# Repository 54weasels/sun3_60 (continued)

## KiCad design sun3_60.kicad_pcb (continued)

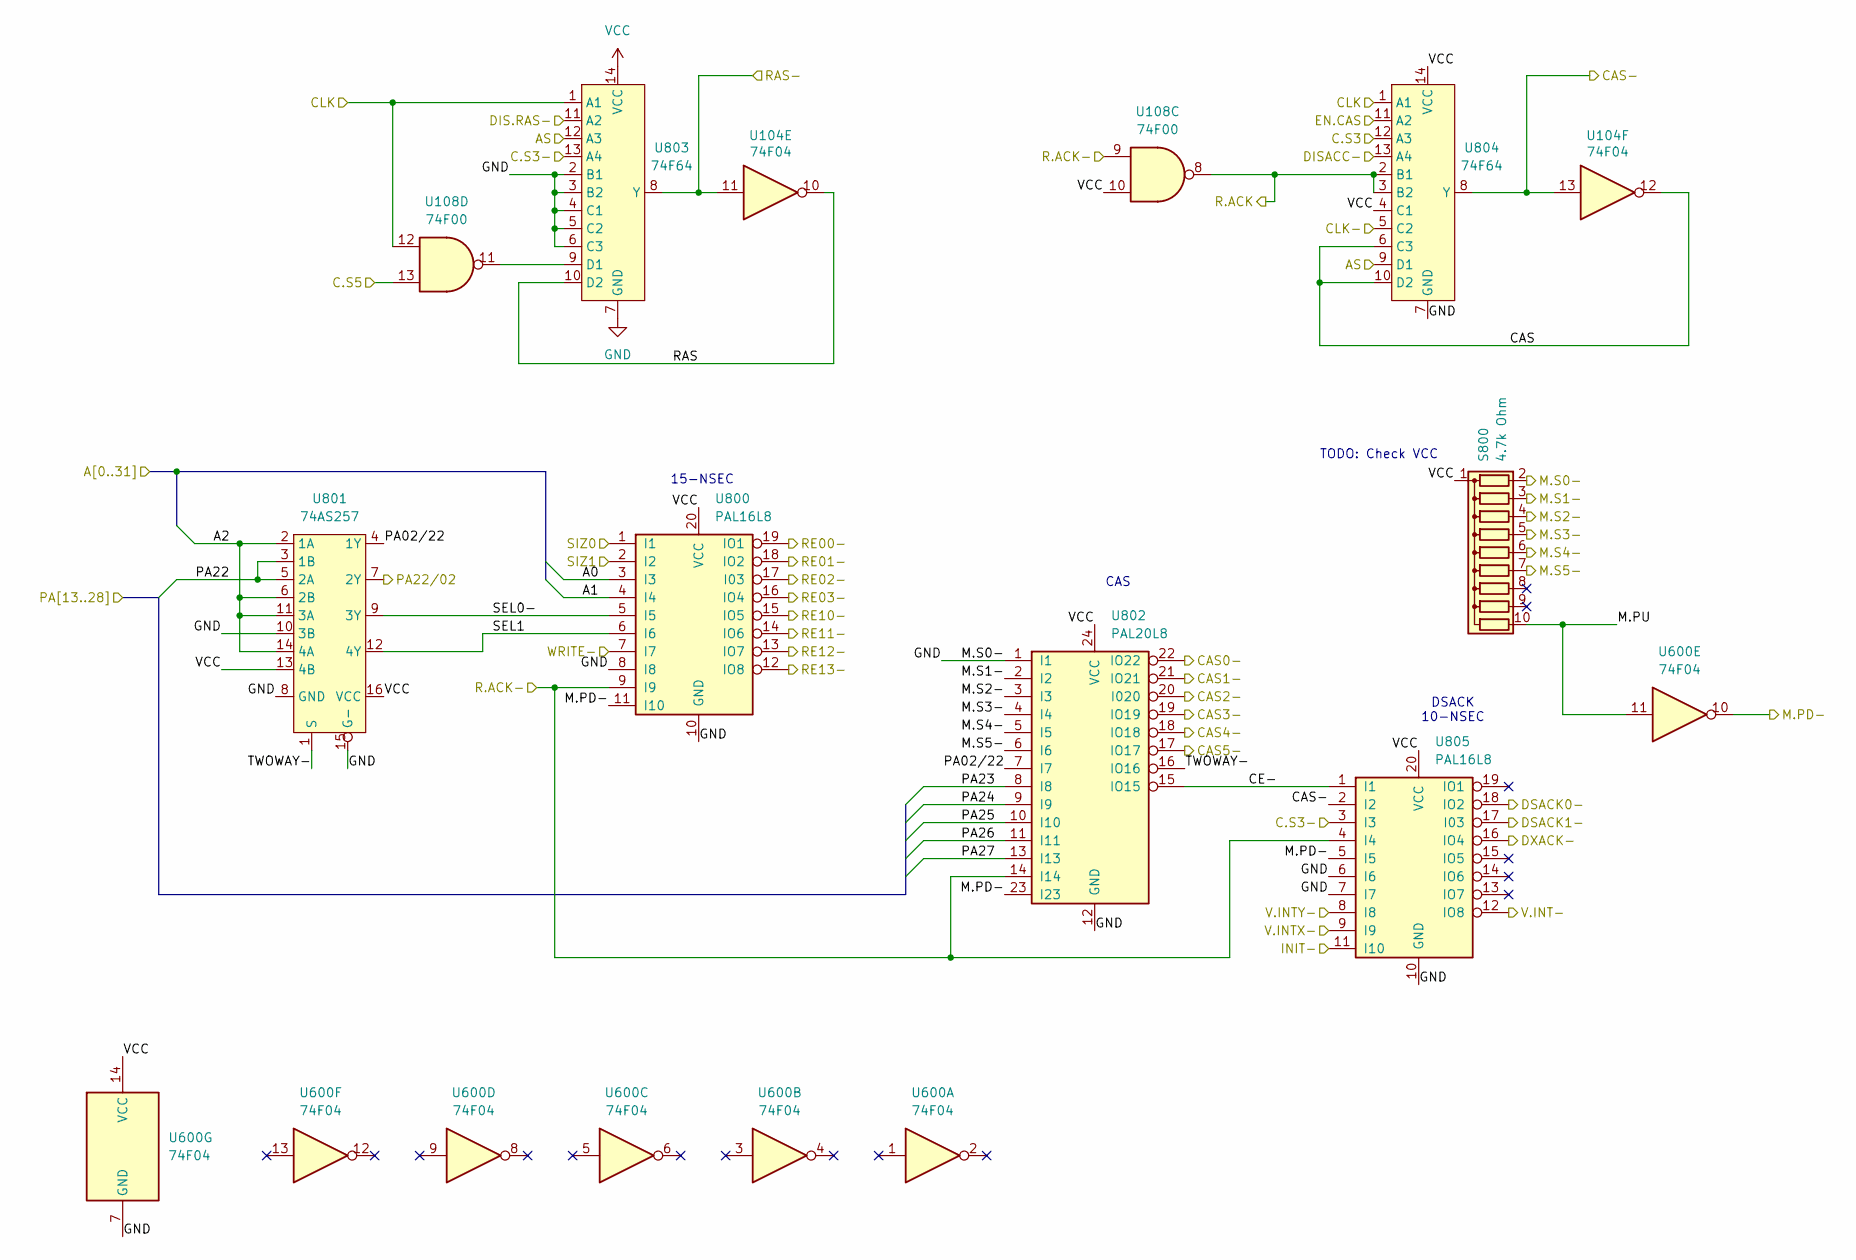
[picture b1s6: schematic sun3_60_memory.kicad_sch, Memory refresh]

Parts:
S800: 4.7k Ohm; R_Array_SIP10
U104, U600: 74F04; DIP-14_W7.62mm
U108: 74F00; DIP-14_W7.62mm
U800, U805: PAL16L8; DIP-20_W7.62mm
U801: 74AS257; DIP-16_W7.62mm
U802: PAL20L8; DIP-24_W7.62mm
U803, U804: 74F64; DIP-14_W7.62mm

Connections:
/AS: U803.12 (A3), U804.9 (D1); also elsewhere on the board
/C.S3: U804.12 (A3); also elsewhere on the board
/C.S3-: U803.13 (A4), U805.3 (I3); also elsewhere on the board
/C.S5: U108.13; also elsewhere on the board
/CAS-: U104.13, U804.8 (Y), U805.2 (I2); also elsewhere on the board
/CLK: U108.12, U803.1 (A1), U804.1 (A1); also elsewhere on the board
/CLK-: U804.5 (C2); also elsewhere on the board
/DIS.RAS-: U803.11 (A2); also elsewhere on the board
/DISACC-: U804.13 (A4); also elsewhere on the board
/DSACK0-: U805.18 (IO2); also elsewhere on the board
/DSACK1-: U805.17 (I03); also elsewhere on the board
/DXACK-: U805.16 (IO4); also elsewhere on the board
/EN.CAS: U804.11 (A2); also elsewhere on the board
/Ethernet/A0: U800.3 (I3); also elsewhere on the board
/Ethernet/A1: U800.4 (I4); also elsewhere on the board
/Ethernet/A2: U801.2 (1A), U801.6 (2B), U801.11 (3A), U801.14 (4A); also elsewhere on the board
/INIT-: U805.11 (I10); also elsewhere on the board
/R.ACK-: U108.9, U800.9 (I9), U802.14 (I14), U805.4 (I4); also elsewhere on the board
/S8A Memory/CAS: U104.12, U804.6 (C3), U804.10 (D2)
/S8A Memory/CAS0-: U802.22 (IO22); also elsewhere on the board
/S8A Memory/CAS1-: U802.21 (IO21)
/S8A Memory/CAS2-: U802.20 (I020)
/S8A Memory/CAS3-: U802.19 (IO19)
/S8A Memory/CAS4-: U802.18 (IO18)
/S8A Memory/CAS5-: U802.17 (IO17)
/S8A Memory/CE-: U802.15 (IO15), U805.1 (I1)
/S8A Memory/M.PD-: U600.10, U800.11 (I10), U802.23 (I23), U805.5 (I5); also elsewhere on the board
/S8A Memory/M.PU: S800.10 (R9), U600.11
/S8A Memory/M.S1-: S800.3 (R2), U802.2 (I2)
/S8A Memory/M.S2-: S800.4 (R3), U802.3 (I3)
/S8A Memory/M.S3-: S800.5 (R4), U802.4 (I4)
/S8A Memory/M.S4-: S800.6 (R5), U802.5 (I5)
/S8A Memory/M.S5-: S800.7 (R6), U802.6 (I6)
/S8A Memory/PA02/22: U801.4 (1Y), U802.7 (I7)
/S8A Memory/PA22: U801.3 (1B), U801.5 (2A); also elsewhere on the board
/S8A Memory/PA22/02: U801.7 (2Y); also elsewhere on the board
/S8A Memory/PA23: U802.8 (I8); also elsewhere on the board
/S8A Memory/PA24: U802.9 (I9); also elsewhere on the board
/S8A Memory/PA25: U802.10 (I10); also elsewhere on the board
/S8A Memory/PA26: U802.11 (I11); also elsewhere on the board
/S8A Memory/PA27: U802.13 (I13); also elsewhere on the board
/S8A Memory/R.ACK: U108.8, U804.2 (B1), U804.3 (B2)
/S8A Memory/RAS: U104.10, U803.10 (D2)
/S8A Memory/RAS-: U104.11, U803.8 (Y); also elsewhere on the board
/S8A Memory/RE00-: U800.19 (IO1); also elsewhere on the board
/S8A Memory/RE01-: U800.18 (IO2); also elsewhere on the board
/S8A Memory/RE02-: U800.17 (I03); also elsewhere on the board
/S8A Memory/RE03-: U800.16 (IO4); also elsewhere on the board
/S8A Memory/RE10-: U800.15 (IO5)
/S8A Memory/RE11-: U800.14 (IO6)
/S8A Memory/RE12-: U800.13 (IO7)
/S8A Memory/RE13-: U800.12 (IO8)
/S8A Memory/SEL0-: U800.5 (I5), U801.9 (3Y)
/S8A Memory/SEL1: U800.6 (I6), U801.12 (4Y)
/S8A Memory/TWOWAY-: U801.1 (S), U802.16 (IO16)
/S8A Memory/V.INTX-: U805.9 (I9)
/S8A Memory/V.INTY-: U805.8 (I8)
/SIZ0: U800.1 (I1); also elsewhere on the board
/SIZ1: U800.2 (I2); also elsewhere on the board
/V.INT-: U805.12 (IO8); also elsewhere on the board
/WRITE-: U800.7 (I7); also elsewhere on the board
GND: S800.2 (R1), U600.7 (GND), U800.8 (I8), U800.10 (GND), U801.8 (GND), U801.10 (3B), U801.15 (G-), U802.1 (I1), U802.12 (GND), U803.2 (B1), U803.3 (B2), U803.4 (C1), U803.5 (C2), U803.6 (C3), U803.7 (GND), U804.7 (GND), U805.6 (I6), U805.7 (I7), U805.10 (GND); also elsewhere on the board
unnamed: U108.11, U803.9 (D1)
VCC: S800.1 (common), U108.10, U600.14 (VCC), U800.20 (VCC), U801.13 (4B), U801.16 (VCC), U802.24 (VCC), U803.14 (VCC), U804.4 (C1), U804.14 (VCC), U805.20 (VCC); also elsewhere on the board

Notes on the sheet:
DSACK 10-NSEC
TODO: Check VCC
CAS
15-NSEC

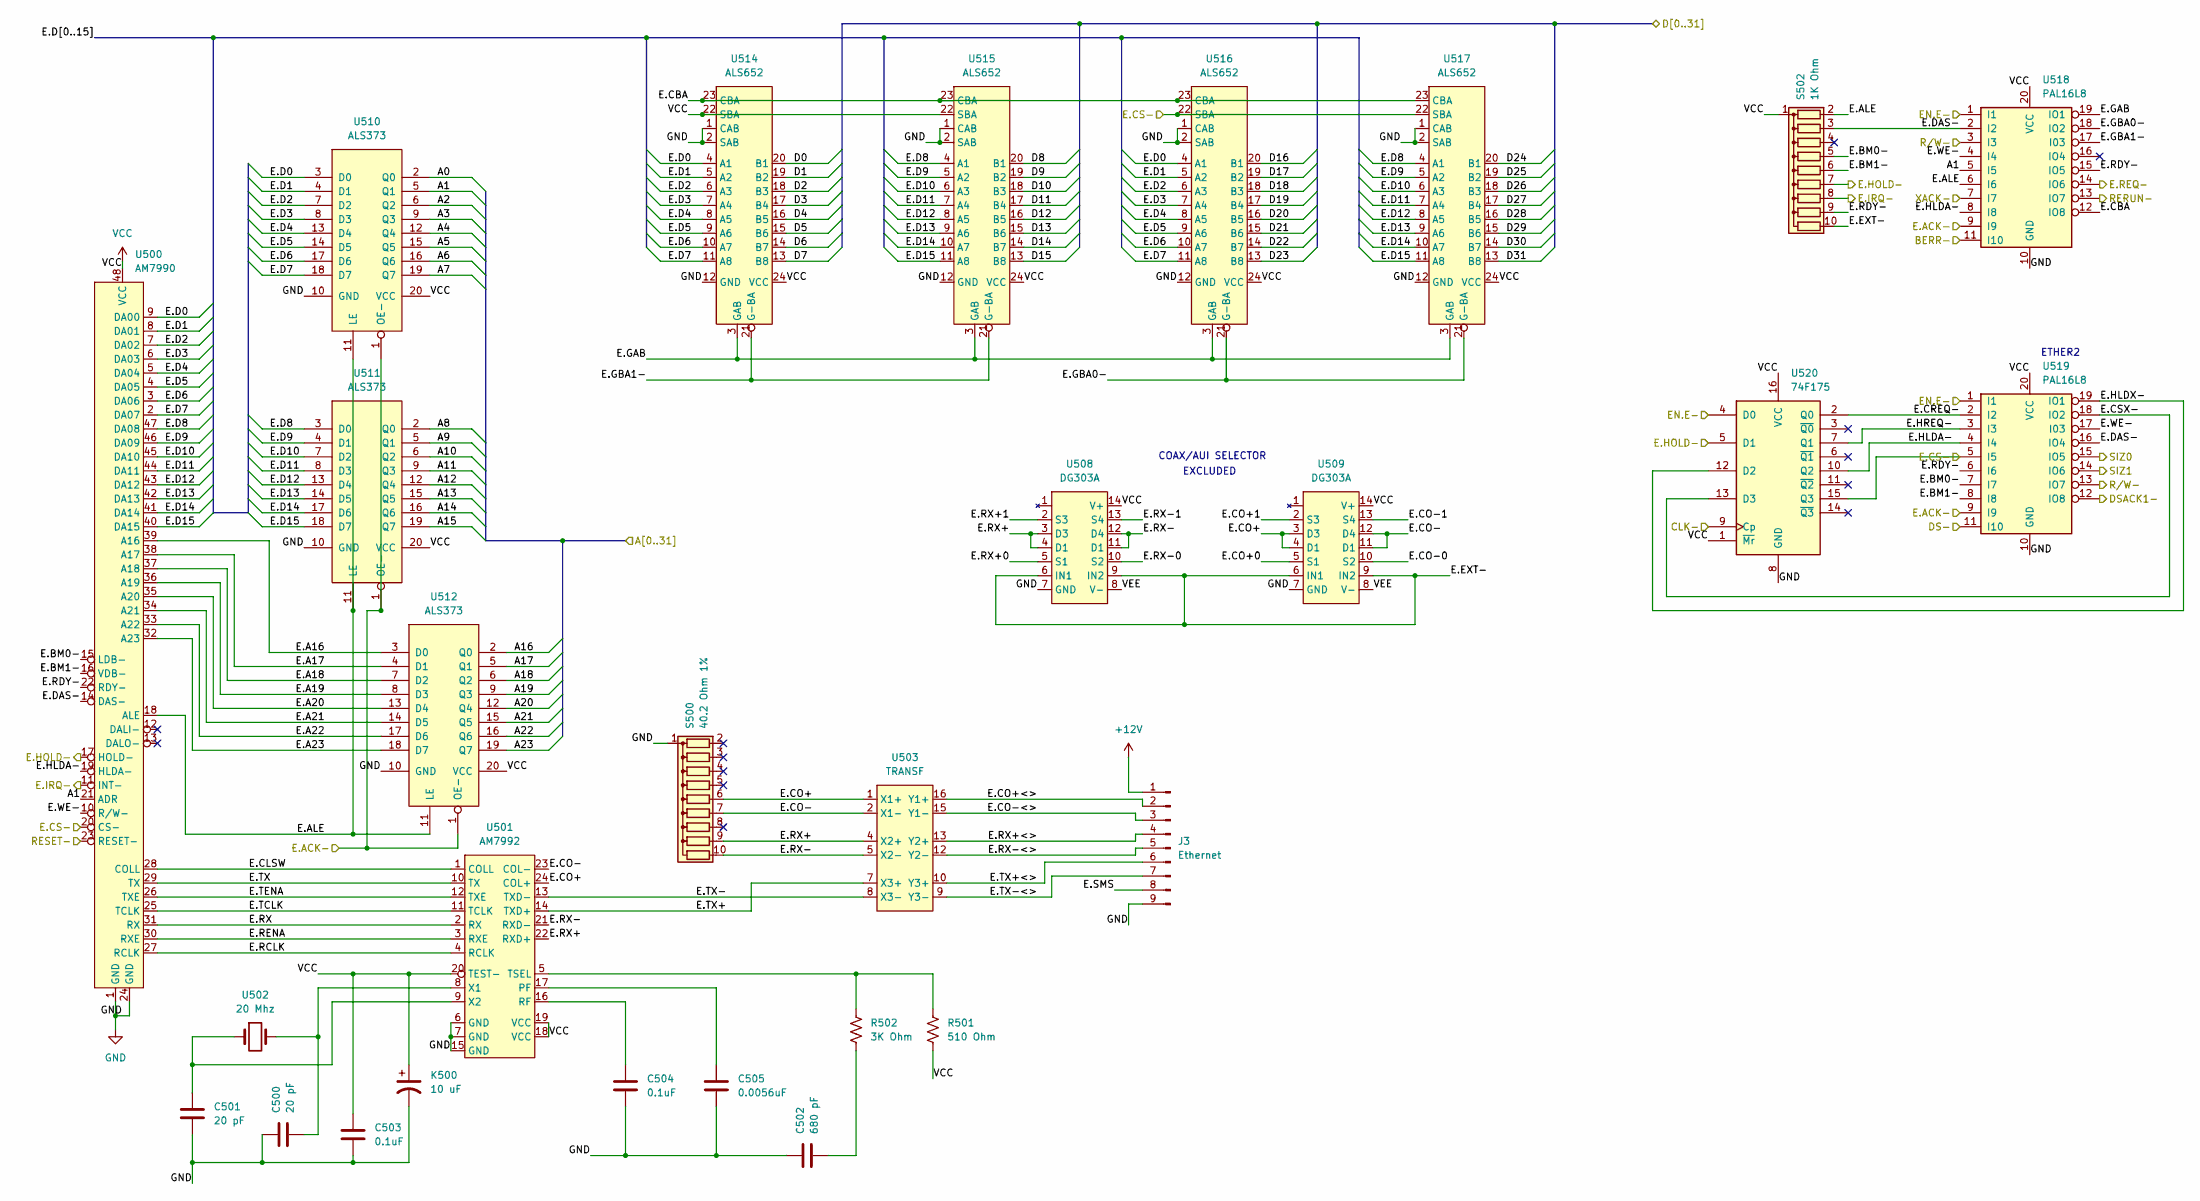
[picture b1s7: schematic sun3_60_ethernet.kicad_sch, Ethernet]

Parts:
C500, C501: 20 pF; C_Rect_L7.0mm_W2.0mm_P5.00mm
C502: 680 pF; C_Rect_L7.0mm_W2.0mm_P5.00mm
C503, C504: 0.1uF; C_Rect_L7.0mm_W2.0mm_P5.00mm
C505: 0.0056uF; C_Rect_L7.0mm_W2.0mm_P5.00mm
J3: Ethernet; PinHeader_1x09_P2.54mm_Vertical
K500: 10 uF; CP_Radial_D10.0mm_P5.00mm
R501: 510 Ohm; R_Axial_DIN0207_L6.3mm_D2.5mm_P7.62mm_Horizontal
R502: 3K Ohm; R_Axial_DIN0207_L6.3mm_D2.5mm_P7.62mm_Horizontal
S500: 40.2 Ohm 1%; R_Array_SIP10
S502: 1K Ohm; R_Array_SIP10
U500: AM7990; DIP-48_W15.24mm
U501: AM7992; DIP-24_W7.62mm
U502: 20 Mhz; Crystal_HC49-U_Vertical
U503: TRANSF; DIP-16_W7.62mm
U508, U509: DG303A; DIP-14_W7.62mm
U510, U511, U512: ALS373
U514, U515, U516, U517: ALS652; DIP-24_W7.62mm
U518, U519: PAL16L8; DIP-20_W7.62mm
U520: 74F175; DIP-16_W7.62mm

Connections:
+12V: J3.1; also elsewhere on the board
/BERR-: U518.11 (I10); also elsewhere on the board
/CLK-: U520.9 (Cp); also elsewhere on the board
/DS-: U519.11 (I10); also elsewhere on the board
/DSACK1-: U519.12 (IO8); also elsewhere on the board
/E.ACK-: U510.1 (OE-), U511.1 (OE-), U512.1 (OE-), U518.9 (I9), U519.9 (I9); also elsewhere on the board
/E.CS-: U500.20 (CS-), U516.22 (SBA), U517.22 (SBA), U519.5 (I5), U520.15 (Q3); also elsewhere on the board
/E.HOLD-: S502.7 (R6), U500.17 (HOLD-), U520.5 (D1); also elsewhere on the board
/E.IRQ-: S502.8 (R7), U500.11 (INT-); also elsewhere on the board
/E.REQ-: U518.14 (IO6); also elsewhere on the board
/EN.E-: U518.1 (I1), U519.1 (I1), U520.4 (D0); also elsewhere on the board
/Ethernet/A0: U510.2 (Q0); also elsewhere on the board
/Ethernet/A1: U500.21 (ADR), U510.5 (Q1), U518.5 (I5); also elsewhere on the board
/Ethernet/A2: U510.6 (Q2); also elsewhere on the board
/Ethernet/A3: U510.9 (Q3); also elsewhere on the board
/Ethernet/A4: U510.12 (Q4); also elsewhere on the board
/Ethernet/A5: U510.15 (Q5); also elsewhere on the board
/Ethernet/A6: U510.16 (Q6); also elsewhere on the board
/Ethernet/A7: U510.19 (Q7); also elsewhere on the board
/Ethernet/A8: U511.2 (Q0); also elsewhere on the board
/Ethernet/A9: U511.5 (Q1); also elsewhere on the board
/Ethernet/A10: U511.6 (Q2); also elsewhere on the board
/Ethernet/A11: U511.9 (Q3); also elsewhere on the board
/Ethernet/A12: U511.12 (Q4); also elsewhere on the board
/Ethernet/A13: U511.15 (Q5); also elsewhere on the board
/Ethernet/A14: U511.16 (Q6); also elsewhere on the board
/Ethernet/A15: U511.19 (Q7); also elsewhere on the board
/Ethernet/A16: U512.2 (Q0); also elsewhere on the board
/Ethernet/A17: U512.5 (Q1); also elsewhere on the board
/Ethernet/A18: U512.6 (Q2); also elsewhere on the board
/Ethernet/A19: U512.9 (Q3); also elsewhere on the board
/Ethernet/A20: U512.12 (Q4); also elsewhere on the board
/Ethernet/A21: U512.15 (Q5); also elsewhere on the board
/Ethernet/A22: U512.16 (Q6); also elsewhere on the board
/Ethernet/A23: U512.19 (Q7); also elsewhere on the board
/Ethernet/E.A16: U500.39 (A16), U512.3 (D0)
/Ethernet/E.A17: U500.38 (A17), U512.4 (D1)
/Ethernet/E.A18: U500.37 (A18), U512.7 (D2)
/Ethernet/E.A19: U500.36 (A19), U512.8 (D3)
/Ethernet/E.A20: U500.35 (A20), U512.13 (D4)
/Ethernet/E.A21: U500.34 (A21), U512.14 (D5)
/Ethernet/E.A22: U500.33 (A22), U512.17 (D6)
/Ethernet/E.A23: U500.32 (A23), U512.18 (D7)
/Ethernet/E.ALE: S502.2 (R1), U500.18 (ALE), U510.11 (LE), U511.11 (LE), U512.11 (LE), U518.6 (I6)
/Ethernet/E.BM0-: S502.5 (R4), U500.15 (LDB-), U519.7 (I7)
/Ethernet/E.BM1-: S502.6 (R5), U500.16 (VDB-), U519.8 (I8)
/Ethernet/E.CBA: U514.23 (CBA), U515.23 (CBA), U516.23 (CBA), U517.23 (CBA), U518.12 (IO8)
/Ethernet/E.CLSW: U500.28 (COLL), U501.1 (COLL)
/Ethernet/E.CO+: S500.6 (R5), U501.24 (COL+), U503.1 (X1+), U509.3 (D3), U509.4 (D1)
/Ethernet/E.CO+<>: J3.2, U503.16 (Y1+)
/Ethernet/E.CO-: S500.7 (R6), U501.23 (COL-), U503.2 (X1-), U509.11 (D1), U509.12 (D4)
/Ethernet/E.CO-<>: J3.3, U503.15 (Y1-)
/Ethernet/E.CREQ-: U519.2 (I2), U520.2 (Q0)
/Ethernet/E.CSX-: U519.18 (IO2), U520.13 (D3)
/Ethernet/E.D0: U500.9 (DA00), U510.3 (D0), U514.4 (A1), U516.4 (A1)
/Ethernet/E.D1: U500.8 (DA01), U510.4 (D1), U514.5 (A2), U516.5 (A2)
/Ethernet/E.D2: U500.7 (DA02), U510.7 (D2), U514.6 (A3), U516.6 (A3)
/Ethernet/E.D3: U500.6 (DA03), U510.8 (D3), U514.7 (A4), U516.7 (A4)
/Ethernet/E.D4: U500.5 (DA04), U510.13 (D4), U514.8 (A5), U516.8 (A5)
/Ethernet/E.D5: U500.4 (DA05), U510.14 (D5), U514.9 (A6), U516.9 (A6)
/Ethernet/E.D6: U500.3 (DA06), U510.17 (D6), U514.10 (A7), U516.10 (A7)
/Ethernet/E.D7: U500.2 (DA07), U510.18 (D7), U514.11 (A8), U516.11 (A8)
/Ethernet/E.D8: U500.47 (DA08), U511.3 (D0), U515.4 (A1), U517.4 (A1)
/Ethernet/E.D9: U500.46 (DA09), U511.4 (D1), U515.5 (A2), U517.5 (A2)
/Ethernet/E.D10: U500.45 (DA10), U511.7 (D2), U515.6 (A3), U517.6 (A3)
/Ethernet/E.D11: U500.44 (DA11), U511.8 (D3), U515.7 (A4), U517.7 (A4)
/Ethernet/E.D12: U500.43 (DA12), U511.13 (D4), U515.8 (A5), U517.8 (A5)
/Ethernet/E.D13: U500.42 (DA13), U511.14 (D5), U515.9 (A6), U517.9 (A6)
/Ethernet/E.D14: U500.41 (DA14), U511.17 (D6), U515.10 (A7), U517.10 (A7)
/Ethernet/E.D15: U500.40 (DA15), U511.18 (D7), U515.11 (A8), U517.11 (A8)
/Ethernet/E.DAS-: S502.3 (R2), U500.14 (DAS-), U518.2 (I2), U519.16 (IO4)
/Ethernet/E.EXT-: S502.10 (R9), U508.6 (IN1), U508.9 (IN2), U509.6 (IN1), U509.9 (IN2)
/Ethernet/E.GAB: U514.3 (GAB), U515.3 (GAB), U516.3 (GAB), U517.3 (GAB), U518.19 (IO1)
/Ethernet/E.GBA0-: U516.21 (G-BA), U517.21 (G-BA), U518.18 (IO2)
/Ethernet/E.GBA1-: U514.21 (G-BA), U515.21 (G-BA), U518.17 (I03)
/Ethernet/E.HLDA-: U500.19 (HLDA-), U518.8 (I8), U519.4 (I4), U520.10 (Q2)
/Ethernet/E.HLDX-: U519.19 (IO1), U520.12 (D2)
/Ethernet/E.HREQ-: U519.3 (I3), U520.7 (Q1)
/Ethernet/E.RCLK: U500.27 (RCLK), U501.4 (RCLK)
/Ethernet/E.RDY-: S502.9 (R8), U500.22 (RDY-), U518.15 (IO5), U519.6 (I6)
/Ethernet/E.RENA: U500.30 (RXE), U501.3 (RXE)
/Ethernet/E.RX: U500.31 (RX), U501.2 (RX)
/Ethernet/E.RX+: S500.9 (R8), U501.22 (RXD+), U503.4 (X2+), U508.3 (D3), U508.4 (D1)
/Ethernet/E.RX+<>: J3.4, U503.13 (Y2+)
/Ethernet/E.RX-: S500.10 (R9), U501.21 (RXD-), U503.5 (X2-), U508.11 (D1), U508.12 (D4)
/Ethernet/E.RX-<>: J3.5, U503.12 (Y2-)
/Ethernet/E.SMS: J3.8
/Ethernet/E.TCLK: U500.25 (TCLK), U501.11 (TCLK)
/Ethernet/E.TENA: U500.26 (TXE), U501.12 (TXE)
/Ethernet/E.TX: U500.29 (TX), U501.10 (TX)
/Ethernet/E.TX+: U501.14 (TXD+), U503.7 (X3+)
/Ethernet/E.TX+<>: J3.6, U503.10 (Y3+)
/Ethernet/E.TX-: U501.13 (TXD-), U503.8 (X3-)
/Ethernet/E.TX-<>: J3.7, U503.9 (Y3-)
/Ethernet/E.WE-: U500.10 (R/W-), U518.4 (I4), U519.17 (I03)
/RERUN-: U518.13 (IO7); also elsewhere on the board
/RESET-: U500.23 (RESET-); also elsewhere on the board
/R/W-: U518.3 (I3), U519.13 (IO7); also elsewhere on the board
/SIZ0: U519.15 (IO5); also elsewhere on the board
/SIZ1: U519.14 (IO6); also elsewhere on the board
/XACK-: U518.7 (I7); also elsewhere on the board
/sun3_60_cpu/D0: U514.20 (B1); also elsewhere on the board
/sun3_60_cpu/D1: U514.19 (B2); also elsewhere on the board
/sun3_60_cpu/D2: U514.18 (B3); also elsewhere on the board
/sun3_60_cpu/D3: U514.17 (B4); also elsewhere on the board
/sun3_60_cpu/D4: U514.16 (B5); also elsewhere on the board
/sun3_60_cpu/D5: U514.15 (B6); also elsewhere on the board
/sun3_60_cpu/D6: U514.14 (B7); also elsewhere on the board
/sun3_60_cpu/D7: U514.13 (B8); also elsewhere on the board
/sun3_60_cpu/D8: U515.20 (B1); also elsewhere on the board
/sun3_60_cpu/D9: U515.19 (B2); also elsewhere on the board
/sun3_60_cpu/D10: U515.18 (B3); also elsewhere on the board
/sun3_60_cpu/D11: U515.17 (B4); also elsewhere on the board
/sun3_60_cpu/D12: U515.16 (B5); also elsewhere on the board
/sun3_60_cpu/D13: U515.15 (B6); also elsewhere on the board
/sun3_60_cpu/D14: U515.14 (B7); also elsewhere on the board
/sun3_60_cpu/D15: U515.13 (B8); also elsewhere on the board
/sun3_60_cpu/D16: U516.20 (B1); also elsewhere on the board
/sun3_60_cpu/D17: U516.19 (B2); also elsewhere on the board
/sun3_60_cpu/D18: U516.18 (B3); also elsewhere on the board
/sun3_60_cpu/D19: U516.17 (B4); also elsewhere on the board
/sun3_60_cpu/D20: U516.16 (B5); also elsewhere on the board
/sun3_60_cpu/D21: U516.15 (B6); also elsewhere on the board
/sun3_60_cpu/D22: U516.14 (B7); also elsewhere on the board
/sun3_60_cpu/D23: U516.13 (B8); also elsewhere on the board
/sun3_60_cpu/D24: U517.20 (B1); also elsewhere on the board
/sun3_60_cpu/D25: U517.19 (B2); also elsewhere on the board
/sun3_60_cpu/D26: U517.18 (B3); also elsewhere on the board
/sun3_60_cpu/D27: U517.17 (B4); also elsewhere on the board
/sun3_60_cpu/D28: U517.16 (B5); also elsewhere on the board
/sun3_60_cpu/D29: U517.15 (B6); also elsewhere on the board
/sun3_60_cpu/D30: U517.14 (B7); also elsewhere on the board
/sun3_60_cpu/D31: U517.13 (B8); also elsewhere on the board
GND: C500.1, C501.2, C502.1, C503.2, C504.2, C505.2, J3.9, K500.2, S500.1 (common), U500.1 (GND), U500.24 (GND), U501.6 (GND), U501.7 (GND), U501.15 (GND), U508.7 (GND), U509.7 (GND), U510.10 (GND), U511.10 (GND), U512.10 (GND), U514.1 (CAB), U514.2 (SAB), U514.12 (GND), U515.1 (CAB), U515.2 (SAB), U515.12 (GND), U516.1 (CAB), U516.2 (SAB), U516.12 (GND), U517.1 (CAB), U517.2 (SAB), U517.12 (GND), U518.10 (GND), U519.10 (GND), U520.8 (GND); also elsewhere on the board
unnamed: C502.2, R502.2
unnamed: C505.1, U501.17 (PF)
unnamed: C504.1, U501.16 (RF)
unnamed: R501.1, R502.1, U501.5 (TSEL)
unnamed: C500.2, U501.8 (X1), U502.2
unnamed: C501.1, U501.9 (X2), U502.1
unnamed: U508.8 (V-), U509.8 (V-)
VCC: C503.1, K500.1, R501.2, S502.1 (common), U500.48 (VCC), U501.18 (VCC), U501.19 (VCC), U501.20 (TEST-), U508.14 (V+), U509.14 (V+), U510.20 (VCC), U511.20 (VCC), U512.20 (VCC), U514.22 (SBA), U514.24 (VCC), U515.22 (SBA), U515.24 (VCC), U516.24 (VCC), U517.24 (VCC), U518.20 (VCC), U519.20 (VCC), U520.1 (~Mr), U520.16 (VCC); also elsewhere on the board

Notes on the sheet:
EXCLUDED
ETHER2
COAX/AUI SELECTOR

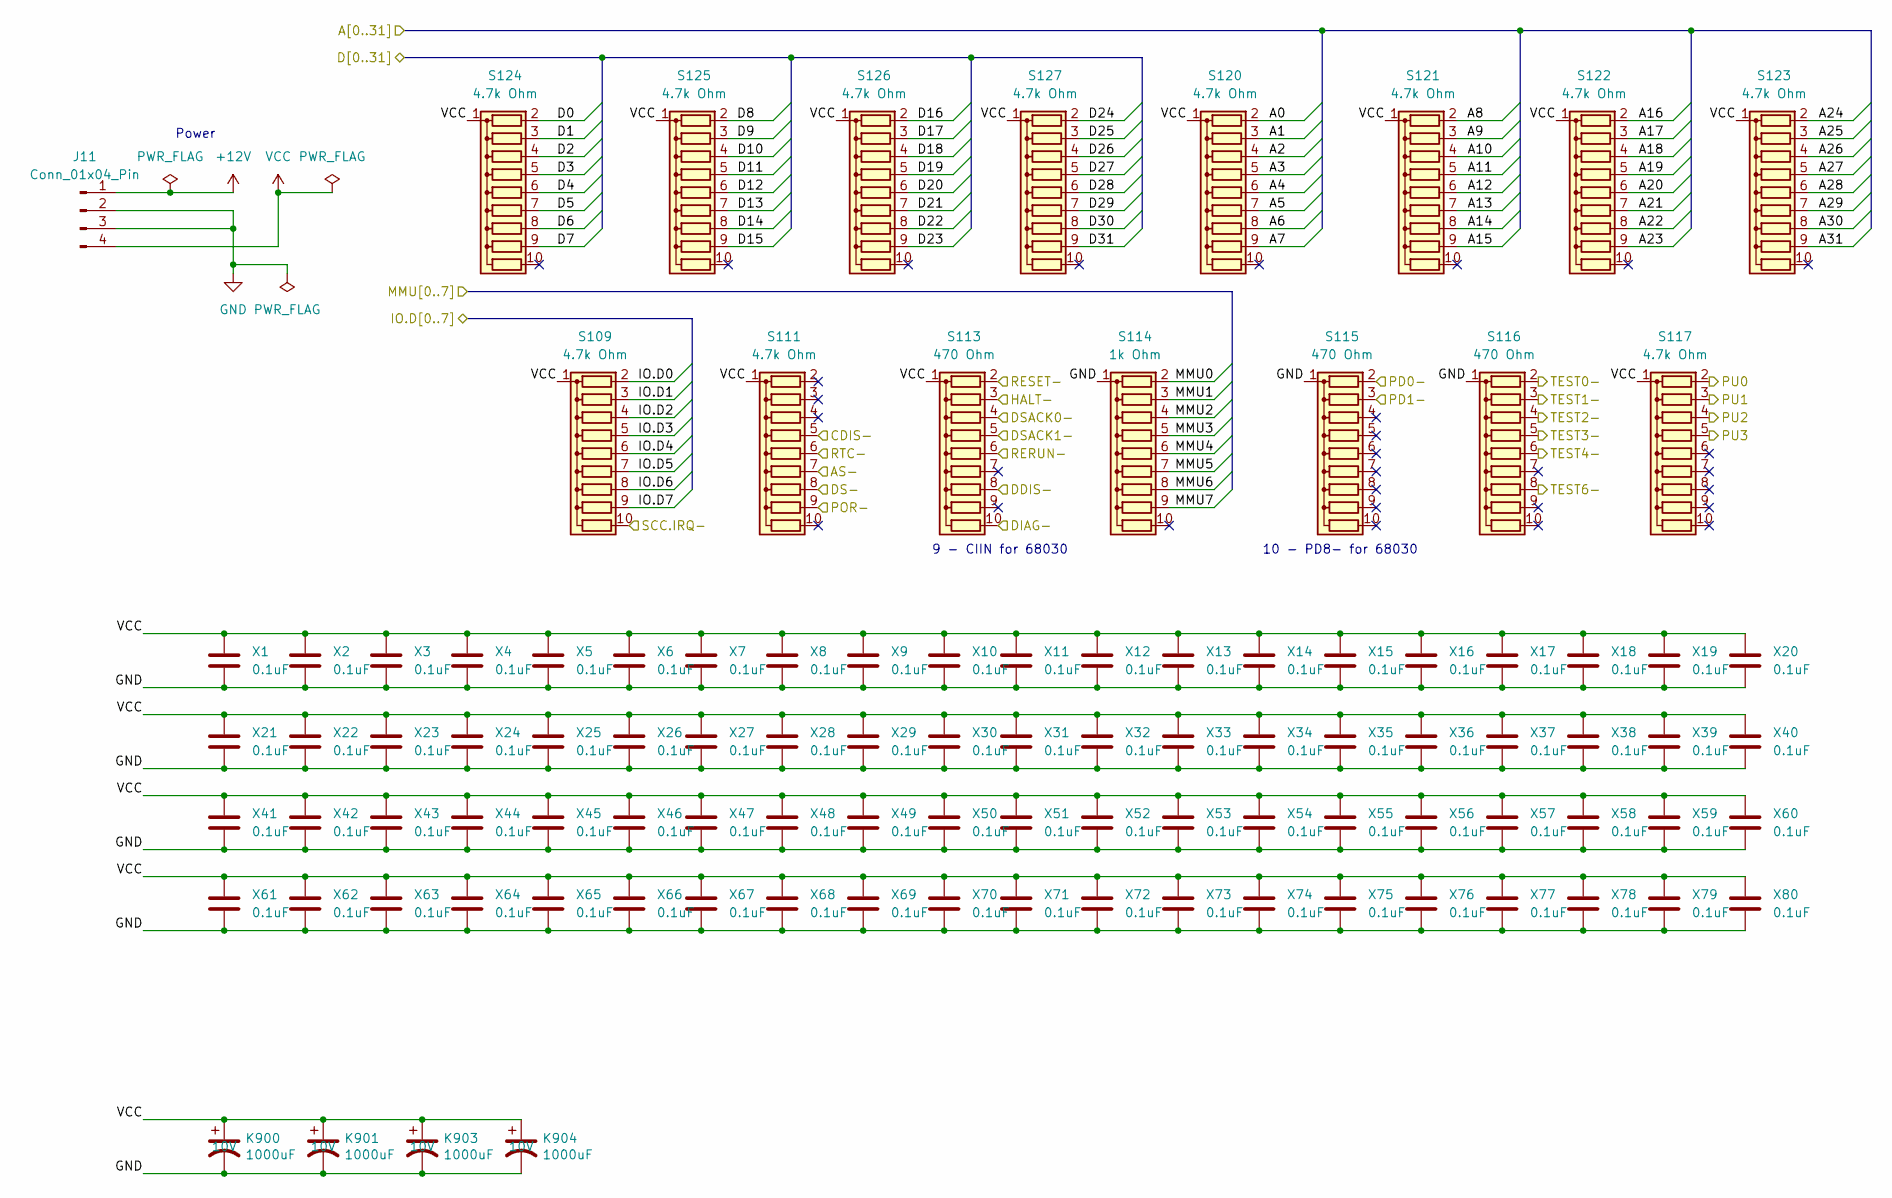
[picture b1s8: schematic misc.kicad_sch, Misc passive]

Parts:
J11: Conn_01x04_Pin; TE_MATE-N-LOK_350211-1_1x04_P5.08mm_Vertical
K900, K901, K903, K904: 1000uF; CP_Radial_D10.0mm_P5.00mm
S109, S111, S117, S120, S121, S122, S123, S124, S125, S126, S127: 4.7k Ohm; R_Array_SIP10
S113, S115, S116: 470 Ohm; R_Array_SIP10
S114: 1k Ohm; R_Array_SIP10
X1, X2, X3, X4, X5, X6, X7, X8, X9, X10, X11, X12, X13, X14, X15, X16, X17, X18, X19, X20, X21, X22, X23, X24, X25, X26, X27, X28, X29, X30, X31, X32, X33, X34, X35, X36, X37, X38, X39, X40, X41, X42, X43, X44, X45, X46, X47, X48, X49, X50, X51, X52, X53, X54, X55, X56, X57, X58, X59, X60, X61, X62, X63, X64, X65, X66, X67, X68, X69, X70, X71, X72, X73, X74, X75, X76, X77, X78, X79, X80: 0.1uF; C_Rect_L7.0mm_W2.0mm_P5.00mm

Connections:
+12V: J11.1; also elsewhere on the board
/AS-: S111.7 (R6); also elsewhere on the board
/CDIS-: S111.5 (R4); also elsewhere on the board
/DDIS-: S113.8 (R7); also elsewhere on the board
/DIAG-: S113.10 (R9); also elsewhere on the board
/DS-: S111.8 (R7); also elsewhere on the board
/DSACK0-: S113.4 (R3); also elsewhere on the board
/DSACK1-: S113.5 (R4); also elsewhere on the board
/Ethernet/A0: S120.2 (R1); also elsewhere on the board
/Ethernet/A1: S120.3 (R2); also elsewhere on the board
/Ethernet/A2: S120.4 (R3); also elsewhere on the board
/Ethernet/A3: S120.5 (R4); also elsewhere on the board
/Ethernet/A4: S120.6 (R5); also elsewhere on the board
/Ethernet/A5: S120.7 (R6); also elsewhere on the board
/Ethernet/A6: S120.8 (R7); also elsewhere on the board
/Ethernet/A7: S120.9 (R8); also elsewhere on the board
/Ethernet/A8: S121.2 (R1); also elsewhere on the board
/Ethernet/A9: S121.3 (R2); also elsewhere on the board
/Ethernet/A10: S121.4 (R3); also elsewhere on the board
/Ethernet/A11: S121.5 (R4); also elsewhere on the board
/Ethernet/A12: S121.6 (R5); also elsewhere on the board
/Ethernet/A13: S121.7 (R6); also elsewhere on the board
/Ethernet/A14: S121.8 (R7); also elsewhere on the board
/Ethernet/A15: S121.9 (R8); also elsewhere on the board
/Ethernet/A16: S122.2 (R1); also elsewhere on the board
/Ethernet/A17: S122.3 (R2); also elsewhere on the board
/Ethernet/A18: S122.4 (R3); also elsewhere on the board
/Ethernet/A19: S122.5 (R4); also elsewhere on the board
/Ethernet/A20: S122.6 (R5); also elsewhere on the board
/Ethernet/A21: S122.7 (R6); also elsewhere on the board
/Ethernet/A22: S122.8 (R7); also elsewhere on the board
/Ethernet/A23: S122.9 (R8); also elsewhere on the board
/Ethernet/A24: S123.2 (R1); also elsewhere on the board
/Ethernet/A25: S123.3 (R2); also elsewhere on the board
/Ethernet/A26: S123.4 (R3); also elsewhere on the board
/Ethernet/A27: S123.5 (R4); also elsewhere on the board
/Ethernet/A28: S123.6 (R5); also elsewhere on the board
/Ethernet/A29: S123.7 (R6); also elsewhere on the board
/Ethernet/A30: S123.8 (R7); also elsewhere on the board
/Ethernet/A31: S123.9 (R8); also elsewhere on the board
/HALT-: S113.3 (R2); also elsewhere on the board
/PD0-: S115.2 (R1); also elsewhere on the board
/PD1-: S115.3 (R2); also elsewhere on the board
/POR-: S111.9 (R8); also elsewhere on the board
/PU0: S117.2 (R1); also elsewhere on the board
/PU1: S117.3 (R2); also elsewhere on the board
/PU2: S117.4 (R3); also elsewhere on the board
/PU3: S117.5 (R4); also elsewhere on the board
/RERUN-: S113.6 (R5); also elsewhere on the board
/RESET-: S113.2 (R1); also elsewhere on the board
/RTC-: S111.6 (R5); also elsewhere on the board
/SCC.IRQ-: S109.10 (R9); also elsewhere on the board
/SCSI 2, Parity/IO.D0: S109.2 (R1); also elsewhere on the board
/SCSI 2, Parity/IO.D1: S109.3 (R2); also elsewhere on the board
/SCSI 2, Parity/IO.D2: S109.4 (R3); also elsewhere on the board
/SCSI 2, Parity/IO.D3: S109.5 (R4); also elsewhere on the board
/SCSI 2, Parity/IO.D4: S109.6 (R5); also elsewhere on the board
/SCSI 2, Parity/IO.D5: S109.7 (R6); also elsewhere on the board
/SCSI 2, Parity/IO.D6: S109.8 (R7); also elsewhere on the board
/SCSI 2, Parity/IO.D7: S109.9 (R8); also elsewhere on the board
/TEST0-: S116.2 (R1); also elsewhere on the board
/TEST1-: S116.3 (R2); also elsewhere on the board
/TEST2-: S116.4 (R3); also elsewhere on the board
/TEST3-: S116.5 (R4); also elsewhere on the board
/TEST4-: S116.6 (R5); also elsewhere on the board
/TEST6-: S116.8 (R7); also elsewhere on the board
/sun3_60_cpu/D0: S124.2 (R1); also elsewhere on the board
/sun3_60_cpu/D1: S124.3 (R2); also elsewhere on the board
/sun3_60_cpu/D2: S124.4 (R3); also elsewhere on the board
/sun3_60_cpu/D3: S124.5 (R4); also elsewhere on the board
/sun3_60_cpu/D4: S124.6 (R5); also elsewhere on the board
/sun3_60_cpu/D5: S124.7 (R6); also elsewhere on the board
/sun3_60_cpu/D6: S124.8 (R7); also elsewhere on the board
/sun3_60_cpu/D7: S124.9 (R8); also elsewhere on the board
/sun3_60_cpu/D8: S125.2 (R1); also elsewhere on the board
/sun3_60_cpu/D9: S125.3 (R2); also elsewhere on the board
/sun3_60_cpu/D10: S125.4 (R3); also elsewhere on the board
/sun3_60_cpu/D11: S125.5 (R4); also elsewhere on the board
/sun3_60_cpu/D12: S125.6 (R5); also elsewhere on the board
/sun3_60_cpu/D13: S125.7 (R6); also elsewhere on the board
/sun3_60_cpu/D14: S125.8 (R7); also elsewhere on the board
/sun3_60_cpu/D15: S125.9 (R8); also elsewhere on the board
/sun3_60_cpu/D16: S126.2 (R1); also elsewhere on the board
/sun3_60_cpu/D17: S126.3 (R2); also elsewhere on the board
/sun3_60_cpu/D18: S126.4 (R3); also elsewhere on the board
/sun3_60_cpu/D19: S126.5 (R4); also elsewhere on the board
/sun3_60_cpu/D20: S126.6 (R5); also elsewhere on the board
/sun3_60_cpu/D21: S126.7 (R6); also elsewhere on the board
/sun3_60_cpu/D22: S126.8 (R7); also elsewhere on the board
/sun3_60_cpu/D23: S126.9 (R8); also elsewhere on the board
/sun3_60_cpu/D24: S127.2 (R1); also elsewhere on the board
/sun3_60_cpu/D25: S127.3 (R2); also elsewhere on the board
/sun3_60_cpu/D26: S127.4 (R3); also elsewhere on the board
/sun3_60_cpu/D27: S127.5 (R4); also elsewhere on the board
/sun3_60_cpu/D28: S127.6 (R5); also elsewhere on the board
/sun3_60_cpu/D29: S127.7 (R6); also elsewhere on the board
/sun3_60_cpu/D30: S127.8 (R7); also elsewhere on the board
/sun3_60_cpu/D31: S127.9 (R8); also elsewhere on the board
/sun3_60_mmu_diag/MMU0: S114.2 (R1); also elsewhere on the board
/sun3_60_mmu_diag/MMU1: S114.3 (R2); also elsewhere on the board
/sun3_60_mmu_diag/MMU2: S114.4 (R3); also elsewhere on the board
/sun3_60_mmu_diag/MMU3: S114.5 (R4); also elsewhere on the board
/sun3_60_mmu_diag/MMU4: S114.6 (R5); also elsewhere on the board
/sun3_60_mmu_diag/MMU5: S114.7 (R6); also elsewhere on the board
/sun3_60_mmu_diag/MMU6: S114.8 (R7); also elsewhere on the board
/sun3_60_mmu_diag/MMU7: S114.9 (R8); also elsewhere on the board
GND: J11.2, J11.3, K900.2, K901.2, K903.2, K904.2, S114.1 (common), S115.1 (common), S116.1 (common), X1.2, X2.2, X3.2, X4.2, X5.2, X6.2, X7.2, X8.2, X9.2, X10.2, X11.2, X12.2, X13.2, X14.2, X15.2, X16.2, X17.2, X18.2, X19.2, X20.2, X21.2, X22.2, X23.2, X24.2, X25.2, X26.2, X27.2, X28.2, X29.2, X30.2, X31.2, X32.2, X33.2, X34.2, X35.2, X36.2, X37.2, X38.2, X39.2, X40.2, X41.2, X42.2, X43.2, X44.2, X45.2, X46.2, X47.2, X48.2, X49.2, X50.2, X51.2, X52.2, X53.2, X54.2, X55.2, X56.2, X57.2, X58.2, X59.2, X60.2, X61.2, X62.2, X63.2, X64.2, X65.2, X66.2, X67.2, X68.2, X69.2, X70.2, X71.2, X72.2, X73.2, X74.2, X75.2, X76.2, X77.2, X78.2, X79.2, X80.2; also elsewhere on the board
VCC: J11.4, K900.1, K901.1, K903.1, K904.1, S109.1 (common), S111.1 (common), S113.1 (common), S117.1 (common), S120.1 (common), S121.1 (common), S122.1 (common), S123.1 (common), S124.1 (common), S125.1 (common), S126.1 (common), S127.1 (common), X1.1, X2.1, X3.1, X4.1, X5.1, X6.1, X7.1, X8.1, X9.1, X10.1, X11.1, X12.1, X13.1, X14.1, X15.1, X16.1, X17.1, X18.1, X19.1, X20.1, X21.1, X22.1, X23.1, X24.1, X25.1, X26.1, X27.1, X28.1, X29.1, X30.1, X31.1, X32.1, X33.1, X34.1, X35.1, X36.1, X37.1, X38.1, X39.1, X40.1, X41.1, X42.1, X43.1, X44.1, X45.1, X46.1, X47.1, X48.1, X49.1, X50.1, X51.1, X52.1, X53.1, X54.1, X55.1, X56.1, X57.1, X58.1, X59.1, X60.1, X61.1, X62.1, X63.1, X64.1, X65.1, X66.1, X67.1, X68.1, X69.1, X70.1, X71.1, X72.1, X73.1, X74.1, X75.1, X76.1, X77.1, X78.1, X79.1, X80.1; also elsewhere on the board

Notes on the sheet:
10 - PD8- for 68030
9 - CIIN for 68030
Power
